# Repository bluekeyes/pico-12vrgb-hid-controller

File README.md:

# pico-12vrgb-hid-controller

A 4-channel 12V-G-R-B controller for RGB fans and LED strips using the Raspberry
Pi Pico and controlled via USB HID. Designed to be installed inside a PC case as
an alternative or addition to motherboard headers.

It implements the "Lighting and Illumination" (`0x59`) HID usage page, making
it fully compatible with the [Dynamic Lighting][] feature in Windows 11.

It also implements the "Sensors" (`0x20`) HID usage page (for a temperature
sensor) and a vendor (`0xFF00`) HID usage page for custom controls.

Note this does *not* support 3-pin addressable RGB LEDs, but uses the
semi-standard 4-pin 12V-G-R-B connector, where all devices connected to a
channel show the same color.

[Dynamic Lighting]: https://support.microsoft.com/en-us/windows/control-your-dynamic-lighting-devices-in-windows-8e8f22e3-e820-476c-8f9d-9ffc7b6ffcd2

## Animations

When running in autonomous mode, the controller implements configurable
animations. Use the CLI to set the parameters or save an animation as the
default for a channel.

### Breathe

Fades a single color on and off. The fade on time, on time, fade off time, and
off time are all configurable.

https://user-images.githubusercontent.com/1745813/233868169-5f5d1403-0b08-4b99-b51f-30fe5f666057.mp4

### Fade

Fades between up to 8 different colors. The fade time and hold time are
configurable.

https://user-images.githubusercontent.com/1745813/233868393-662b7a13-106e-483d-9052-4a47977f7780.mp4

## Project Structure

This project is split into three parts:

* `hw/` contains schematics and PCB files (KiCAD)
* `fw/` contains device firmware (C)
* `cli/` contains the command-line control program (Rust)

See each directory for more details.

## Limitations

The hardware is only tested on Windows 11, using both the Dynamic Lighting
feature and the included CLI. The CLI does not support other platforms yet. 

## License

MIT

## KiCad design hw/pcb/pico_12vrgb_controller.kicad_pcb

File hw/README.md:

# Hardware

This directory contains design files for the controller hardware:

* `pcb` - a KiCAD 7.x project with the schematic and PCB design
* `case` - OpenSCAD and STL files for a simple 3D printed case for the PCB

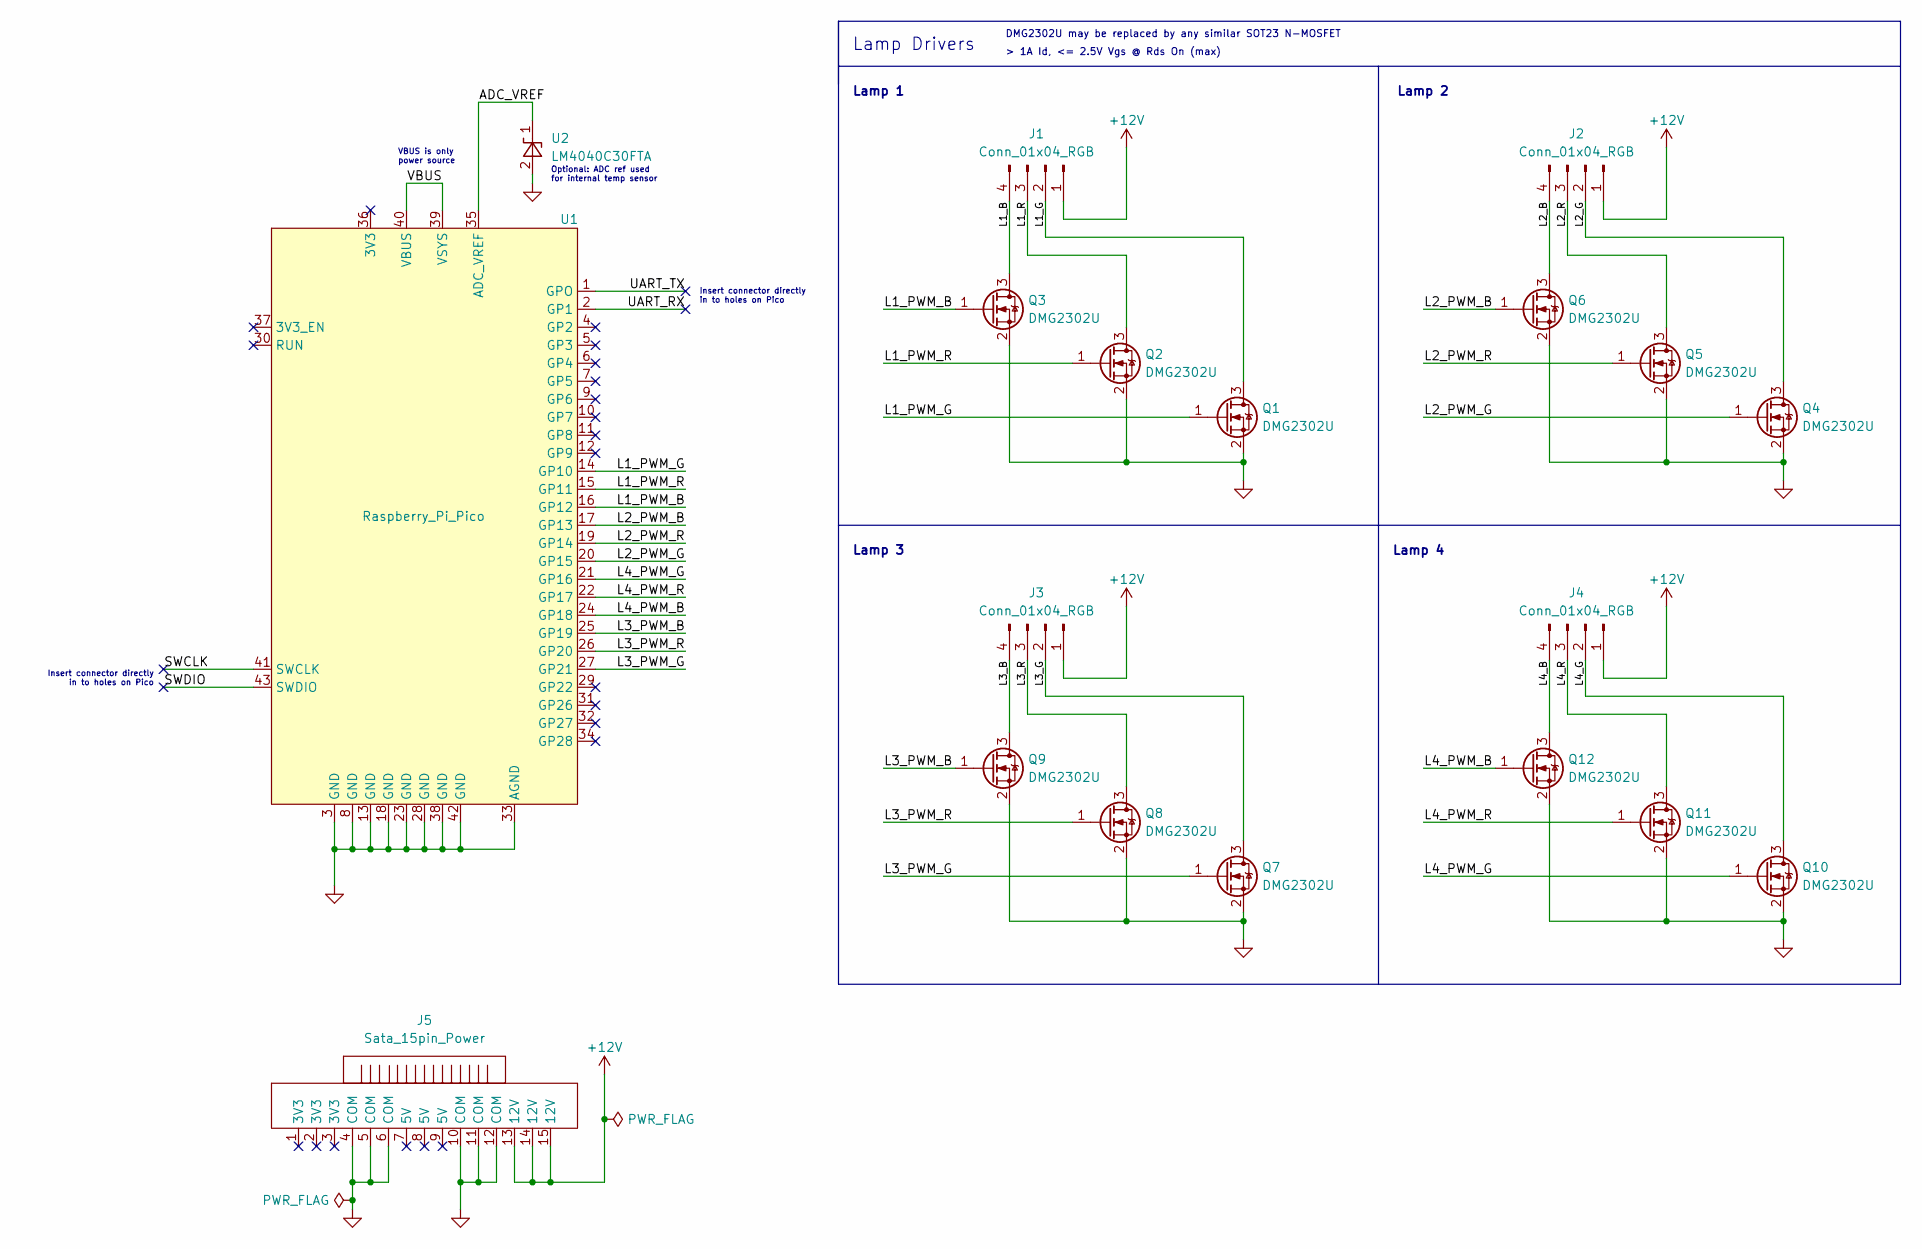
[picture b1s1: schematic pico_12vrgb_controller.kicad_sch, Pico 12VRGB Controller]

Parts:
J1, J2: Conn_01x04_RGB; PinHeader_12VGRB_Vertical_LeftText
J3, J4: Conn_01x04_RGB; PinHeader_12VGRB_Vertical_RightText
J5: Sata_15pin_Power; ModDIY_SATA_15pin_RightAngle_Header
Q1, Q2, Q3, Q4, Q5, Q6, Q7, Q8, Q9, Q10, Q11, Q12: DMG2302U; SOT-23
U1: Raspberry_Pi_Pico; RPi_Pico_SMD
U2: LM4040C30FTA; SOT-23

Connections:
+12V: J1.1, J2.1, J3.1, J4.1, J5.13 (12V), J5.14 (12V), J5.15 (12V)
/ADC_VREF: U1.35 (ADC_VREF), U2.1 (K)
/L1_B: J1.4, Q3.3 (D)
/L1_G: J1.2, Q1.3 (D)
/L1_PWM_B: Q3.1 (G), U1.16 (GP12)
/L1_PWM_G: Q1.1 (G), U1.14 (GP10)
/L1_PWM_R: Q2.1 (G), U1.15 (GP11)
/L1_R: J1.3, Q2.3 (D)
/L2_B: J2.4, Q6.3 (D)
/L2_G: J2.2, Q4.3 (D)
/L2_PWM_B: Q6.1 (G), U1.17 (GP13)
/L2_PWM_G: Q4.1 (G), U1.20 (GP15)
/L2_PWM_R: Q5.1 (G), U1.19 (GP14)
/L2_R: J2.3, Q5.3 (D)
/L3_B: J3.4, Q9.3 (D)
/L3_G: J3.2, Q7.3 (D)
/L3_PWM_B: Q9.1 (G), U1.25 (GP19)
/L3_PWM_G: Q7.1 (G), U1.27 (GP21)
/L3_PWM_R: Q8.1 (G), U1.26 (GP20)
/L3_R: J3.3, Q8.3 (D)
/L4_B: J4.4, Q12.3 (D)
/L4_G: J4.2, Q10.3 (D)
/L4_PWM_B: Q12.1 (G), U1.24 (GP18)
/L4_PWM_G: Q10.1 (G), U1.21 (GP16)
/L4_PWM_R: Q11.1 (G), U1.22 (GP17)
/L4_R: J4.3, Q11.3 (D)
/SWCLK: U1.41 (SWCLK)
/SWDIO: U1.43 (SWDIO)
/UART_RX: U1.2 (GP1)
/UART_TX: U1.1 (GPO)
/VBUS: U1.39 (VSYS), U1.40 (VBUS)
GND: J5.4 (COM), J5.5 (COM), J5.6 (COM), J5.10 (COM), J5.11 (COM), J5.12 (COM), Q1.2 (S), Q2.2 (S), Q3.2 (S), Q4.2 (S), Q5.2 (S), Q6.2 (S), Q7.2 (S), Q8.2 (S), Q9.2 (S), Q10.2 (S), Q11.2 (S), Q12.2 (S), U1.3 (GND), U1.8 (GND), U1.13 (GND), U1.18 (GND), U1.23 (GND), U1.28 (GND), U1.33 (AGND), U1.38 (GND), U1.42 (GND), U2.2 (A)

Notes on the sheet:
Lamp 2
Lamp Drivers
> 1A Id, <= 2.5V Vgs @ Rds On (max)
Insert connector directly in to holes on Pico
DMG2302U may be replaced by any similar SOT23 N-MOSFET
Optional: ADC ref used for internal temp sensor
Lamp 4
Lamp 1
VBUS is only power source
Lamp 3

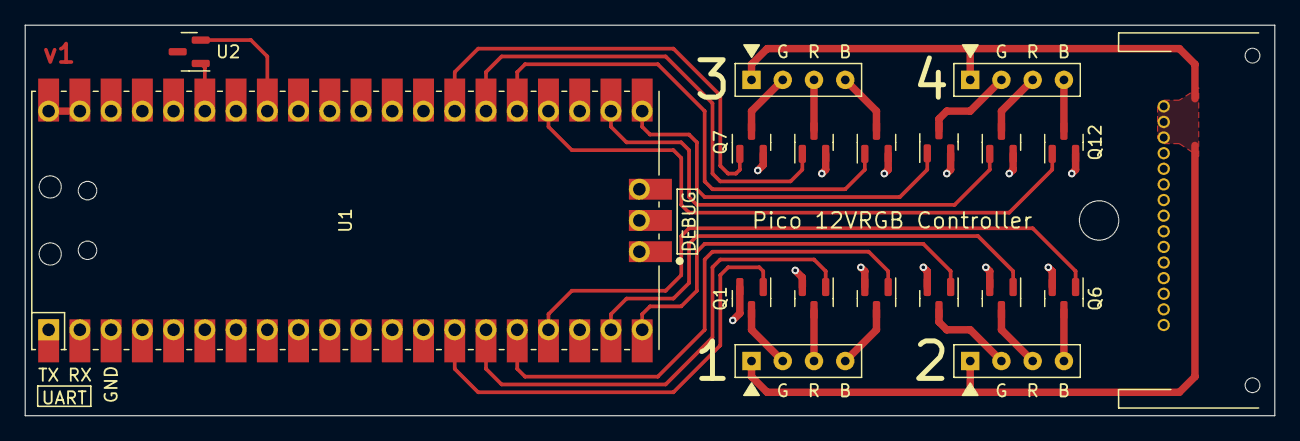
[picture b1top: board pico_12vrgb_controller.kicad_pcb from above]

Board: 2 copper layers, 101.6 x 31.8 mm, 19 parts (0 on the bottom side), 28 nets.

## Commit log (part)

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2022-12-31 Initial commit of generated project
2022-12-31 Move source files to src directory
2022-12-31 Add tusb_config.h to configure TinyUSB
    I've reduced this to only the properties that I believe are required, as
    the example file contains a lot of stuff that is only needed when
    supporting multiple target boards.
2023-01-02 Add usage constants for HID lighting page
2023-01-03 Add vendor HID usages and reports
    For now, the only report is a way to restart the controller in BOOTSEL
    mode for programming, but I think there will eventually be other reports
    for modifying internal settings, picking hardware animations, etc.
2023-01-03 Improve loading of serial number string
    Initially, I wanted to only load this once and save it, but I think
    string descriptors are read infrequently, so it's probably better to
    save memory at the cost of execution time.
2023-01-04 Implement HID get report callback
2023-01-04 Add set report handlers
    Implement the bootsel and lamp attributes reports, the rest are stubs
    for now.
2023-01-05 Move device state to new controller_t struct
    This will also define all the logic for the device, so that it's not
    implemented directly in the USB callbacks.
2023-01-06 Fix PWM initialization
    Operator precedence got me, equality comes before bitwise AND.
2023-01-06 Add simple test script for USB functionality
2023-01-07 Queue lamp updates and run them in main loop
    This better matches the Lighting and Illumination spec and prepares for
    running internal animations out of the main loop as well.
2023-01-07 Implement LampRangeUpdate report handler
2023-01-07 Add autonomous mode function to test script
2023-01-09 Add generic animation support, starting with fades
    Define new animations with a data struct and a frame function. The
    controller managages animation playback, generating new frames as
    needed.
    I still need to figure out how assigning animations to channels should
    work and add the USB functionality for configuring them.
2023-01-09 Support up to 8 target colors in fade animations
2023-01-09 Remove typedefs for simple integer types
    Use uint8_t directly for both lamp IDs and RGB levels
2023-01-09 Remove rgb.h, refactor config references
    Move most of the functionality in rgb.h to lamp.h, which better reflects
    what it actually does. As part of this, create device/specs.h as the One
    True Way to reference configuration. This includes the existing config.h
    file and also defines properties that aren't actually configurable, like
    the lamp count.
2023-01-11 Add vendor HID reports to set animations
    This includes a stubbed function to set a default animation that runs on
    boot, but this isn't implemented yet.
2023-01-12 Create function to set animation from reports
2023-01-16 Simplify animation commands in test.py
2023-01-16 Validate lamp update reports before applying
2023-01-16 Clarify TODO about USB vid/pid
2023-01-17 Update test.py to set default animations
2023-01-17 Revert to using control endpoint for output
    Adding the interrupt out endpoint broke discovery of lighting and
    illumination device via hidapi in Windows, but it still appeared in
    Device Manager, so I'm not sure what's wrong. Go back to the
    configuration that works for now.
2023-01-22 Disable lamps on USB host suspend
    In the future, I might add support for a special animation or something
    while suspended, but I suspect that would also require powering the Pico
    off of the +5V input from the PSU instead of just using VBUS from the
    USB connection. Right now, I'm not planning to support that to simplify
    the PCB (since USB is required for everything else anyway.)
2023-01-24 Add custom model and footprint for SATA connector
    I might need to change this, because the ModDIY listing shows two
    different connectors in the pictures, but only has one data sheet
    picture. Hopefully both connectors work with the same footprint.
2023-01-29 Add temperature sensor to HID report
    The primary purpose for this usage is to trick Windows into leaving the
    device in the active state until there is a global suspend as part of
    going to sleep. By default, Windows selectively suspends the device when
    the bus is idle for a few seconds. I believe this is because nothing
    uses the lighting or vendor pages by default, so there are no open
    connections to the device. To avoid a special driver or service that's
2023-01-29 Simplify USB string descriptors
    The pico-sdk, in the pico_stdio_usb library, has a cleaner
    implementation than the one I derived from the tinyUSB examples. Rewrite
    the version here based on that example.
2023-01-30 Update test script for new animation format
2023-01-30 Start routing PCB, change header orientation
    The RGB half is mostly complete, although I might shift things around to
    save a bit of space. Still need to connect things up to the Pico.
2023-02-01 Fix 12V fill, minor PCB layout tweaks
    Clean up silkscreen, fix remaining DRC errors, expand pads on RGB header
    footprints, make the board slightly shorter on the USB end.
2023-02-02 Clamp RGB values when converting from oklab
    I neglected the fact that when transitioning between certain colors in
    oklab space, the resulting RGB values may be outside of [0.0, 1.0]. This
    meant that the naive cast to uint8_t overflowed and created weird jumps
    in color. Cast to a uint16_t instead, then clamp to the uint8_t range.
2023-02-03 Add report structs for temperature reports
2023-02-03 Add stub handlers for USB temperature reports
2023-02-04 Implement sensor control and temperature reports
    Default to sending async reports every second, but respect the host
    requests for report interval and reporting state. Accept power state
    changes, but these don't do anything.
2023-02-05 Update lighting reports to better match spec
    I found an example descriptor in the original proposal for this page
    that indicates many of these reports should be feature reports, not
    input/output reports and also pointed out some places where I got the
    field sizes wrong.
    I'm not sure if these are actually critical, but Windows is refusing to
    open my device, and one theory is that something is wrong with my
2023-02-06 Fix HID_LOGICAL_MAX widths
    Because parsers assume all fields are signed, to set the logical maximum
    to UINT8_MAX, you must use two byte field, and similarly for UINT16_MAX.
    I got this wrong originally, fixed it, and then undid the fix earlier
    today because I forgot why the fields had to be wider.
2023-02-11 Upgrade to pico-sdk 1.5.0
2023-02-15 Add skeleton Rust project for CLI
2023-02-20 Define remaining command structs
2023-02-20 Add stubs for multi-platform device access
2023-02-21 Implement the reset command for Windows
    Use the WinRT APIs for now, since they're easier. For the LampArray
    commands, this will mean breaking abstraction and generating report
    data directly due to API limitations. But the CLI is meant for a single
    device and the end goal is to use the Lights API anyway.
2023-02-22 Abstract report building for Windows
    Add a trait to cover the difference between different HID report types
    and implement a custom type for writing report data that handles byte
    order and padding correctly.
2023-02-22 Implement get-temperature command
    Only works in one-shot mode, the interval argument is ignored.
2023-02-23 Implement lamp array update commands
    Assume the binary format used by the pico-12vrgb-controller firmware for
    now. This should eventually use the Windows.Devices.Lights API, if the
    hang when opening devices is ever fixed (or I figure out what's wrong.)
2023-02-24 Clean up existing command implementations
    Reorganize some constants and files, simplify report ID mapping.
2023-02-25 Add TODO note about extending the persist format
2023-02-25 Remove nested switches in HID report handlers
2023-02-26 Implement set-animation commands
    Also fix some clippy warnings and clean up some related functions.
2023-02-26 Add struct for LampArrayUpdateFlags
    Also convert the reset report to follow the same pattern.
2023-02-26 Add README for cli subproject
2023-02-27 Turn off lights when setting the 'none' animation
2023-02-28 Add optional debug logging for fade animations
2023-03-01 Fix issue with off state in breathe animations
    I misunderstood how the Oklab space works. While L=0 does mean "zero
    lightness", if a and b are non-zero, the resulting color is outside of
    the normal RGB space and may not be physically possible. I don't think
    it is possible to fade to true black while going "through" some other
    color without adding another stop in the gradient. I don't want to add
    support for that right now, so simplify the animation to fade between
2023-03-04 Use Pico SDK time functions for animations
2023-03-05 Always accept sRGB values, linearize on device
    This makes the vendor interface more consistent with the Lighting and
    Illumination interface and avoids possible issues from lack of bit-depth
    when linearizing in 8-bit values.
2023-03-11 Update SATA footprint based on physical part
    Update minor dimensions in the 3D model, fix solder mask covering the
    holes in the footprint, and add the repository URL to the board.
2023-03-11 Add plotted gerber files for the PCB
2023-03-12 Add 3D model for Pi Pico footprint
    Colors are kind of messed up, possibly due to limits in the STEP file
    format or maybe because of issues with the Fusion 360 export. In either
    case, it's better than nothing.
2023-03-25 Add chamfers to case
    Makes the case look a bit nicer, but doesn't impact function. Also
    confirm the dimensions of the screw hole.
2023-03-29 Update status and add missing READMEs
2023-04-16 Adjust offset for temperature sensor
2023-04-23 Fix VID/PID in test.py
2023-11-17 Fix lighting HID descriptor for Windows
    The Windows 11 implementation of the Lighting & Illumination page
    apparently requires that devices report a descriptor that exactly
    matches the example given in the original HUTRR84 proposal. When given a
    descriptor that does not match this example, the Windows APIs just hang,
    which is not very helpful for debugging.
    While I think my implementation was largely correct given what the HID
2023-11-17 Update CLI and test.py for new report formats
    The CLI should really use the Windows HID APIs now that they should
    work, but that's a larger refactor.
2023-11-17 Fix lamp IDs for vendor commands
2023-11-18 Enable additional compiler errors
    Add -Wextra and -Wconversion, then fix resulting errors. I was most
    interested in implicit conversions as a result of changing the lamp ID
    type in the HID reports.
2023-11-18 Fix report types for lamp updates
    As part of fixing the descriptor, I changed these to feature reports
    instead of output reports, but forgot to fix the handling code that
    actually responds to the reports.
2023-11-18 Bump rustix from 0.36.8 to 0.36.17 in /cli
    Bumps [rustix](https://github.com/bytecodealliance/rustix) from 0.36.8 to 0.36.17.
    - [Release notes](https://github.com/bytecodealliance/rustix/releases)
    - [Commits](https://github.com/bytecodealliance/rustix/compare/v0.36.8...v0.36.17)
    ---
    updated-dependencies:
    - dependency-name: rustix
2023-11-18 Bump rustix from 0.36.8 to 0.36.17 in /cli (#6)
    Bumps [rustix](https://github.com/bytecodealliance/rustix) from 0.36.8 to 0.36.17.
    - [Release notes](https://github.com/bytecodealliance/rustix/releases)
    - [Commits](https://github.com/bytecodealliance/rustix/compare/v0.36.8...v0.36.17)
    ---
    updated-dependencies:
    - dependency-name: rustix
